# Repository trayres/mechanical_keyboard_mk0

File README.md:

# mechanical_keyboard_mk0
A first attempt at a mechanical keyboard.

References:
https://medium.com/@monkeytypewritr/building-your-own-keyboard-from-scratch-bd0638c40850
https://github.com/ruiqimao/keyboard-pcb-guide#schematics

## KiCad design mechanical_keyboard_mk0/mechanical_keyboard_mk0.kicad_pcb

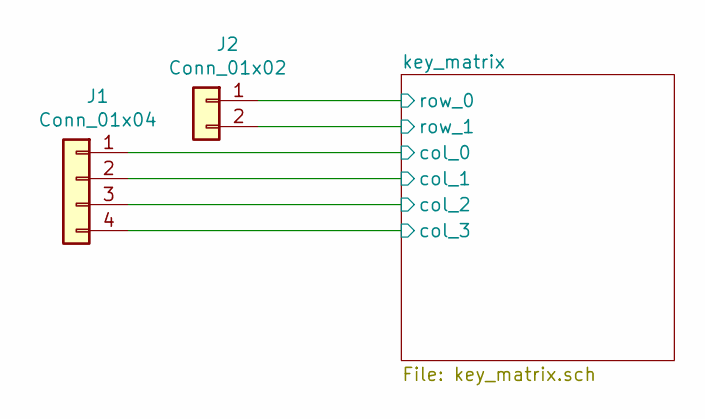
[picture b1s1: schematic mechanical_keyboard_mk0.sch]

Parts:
J1: Conn_01x04; PinHeader_1x04_P2.54mm_Vertical
J2: Conn_01x02; PinHeader_1x02_P2.54mm_Vertical

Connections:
/key_matrix/col_0: J1.1; also elsewhere on the board
/key_matrix/col_1: J1.2; also elsewhere on the board
/key_matrix/col_2: J1.3; also elsewhere on the board
/key_matrix/col_3: J1.4; also elsewhere on the board
/key_matrix/row_0: J2.1; also elsewhere on the board
/key_matrix/row_1: J2.2; also elsewhere on the board

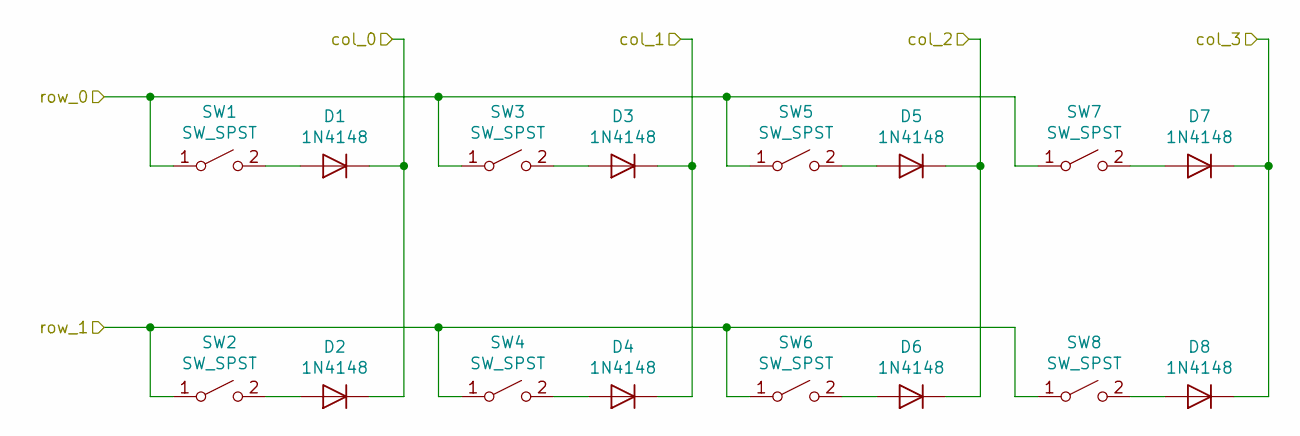
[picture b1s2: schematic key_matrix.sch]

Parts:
D1, D2, D3, D4, D5, D6, D7, D8: 1N4148; D_DO-35_SOD27_P7.62mm_Horizontal
SW1, SW2, SW3, SW4, SW5, SW6, SW7, SW8: SW_SPST; SW_Cherry_MX_1.00u_PCB

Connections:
/key_matrix/col_0: D1.1 (K), D2.1 (K); also elsewhere on the board
/key_matrix/col_1: D3.1 (K), D4.1 (K); also elsewhere on the board
/key_matrix/col_2: D5.1 (K), D6.1 (K); also elsewhere on the board
/key_matrix/col_3: D7.1 (K), D8.1 (K); also elsewhere on the board
/key_matrix/row_0: SW1.1 (A), SW3.1 (A), SW5.1 (A), SW7.1 (A); also elsewhere on the board
/key_matrix/row_1: SW2.1 (A), SW4.1 (A), SW6.1 (A), SW8.1 (A); also elsewhere on the board
unnamed: D1.2 (A), SW1.2 (B)
unnamed: D2.2 (A), SW2.2 (B)
unnamed: D3.2 (A), SW3.2 (B)
unnamed: D4.2 (A), SW4.2 (B)
unnamed: D5.2 (A), SW5.2 (B)
unnamed: D6.2 (A), SW6.2 (B)
unnamed: D7.2 (A), SW7.2 (B)
unnamed: D8.2 (A), SW8.2 (B)

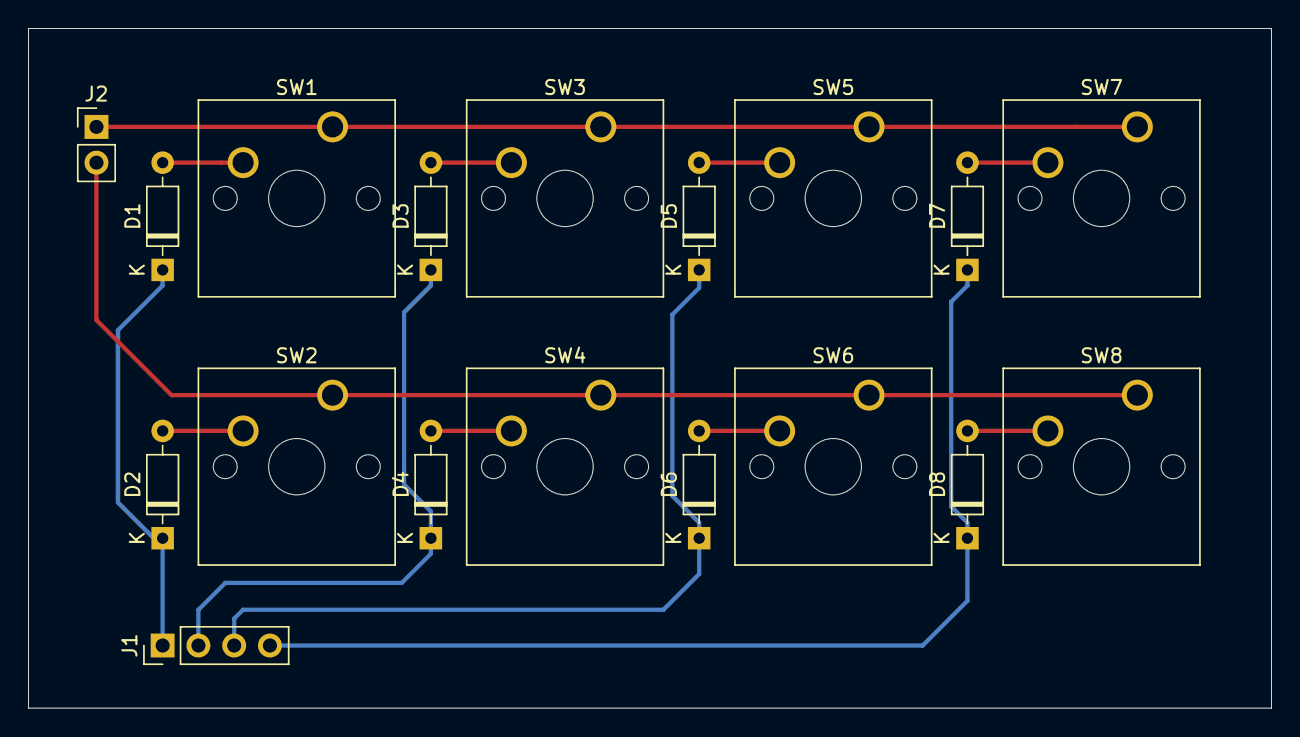
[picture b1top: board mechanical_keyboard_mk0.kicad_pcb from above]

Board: 2 copper layers, 88.3 x 48.3 mm, 18 parts (0 on the bottom side), 14 nets.

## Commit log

2019-05-28 Added a few footprints, started a layout. Kicad sucks.
2019-05-30 Updated to 2 rows.
2019-05-30 Updated layout, created first output job.
